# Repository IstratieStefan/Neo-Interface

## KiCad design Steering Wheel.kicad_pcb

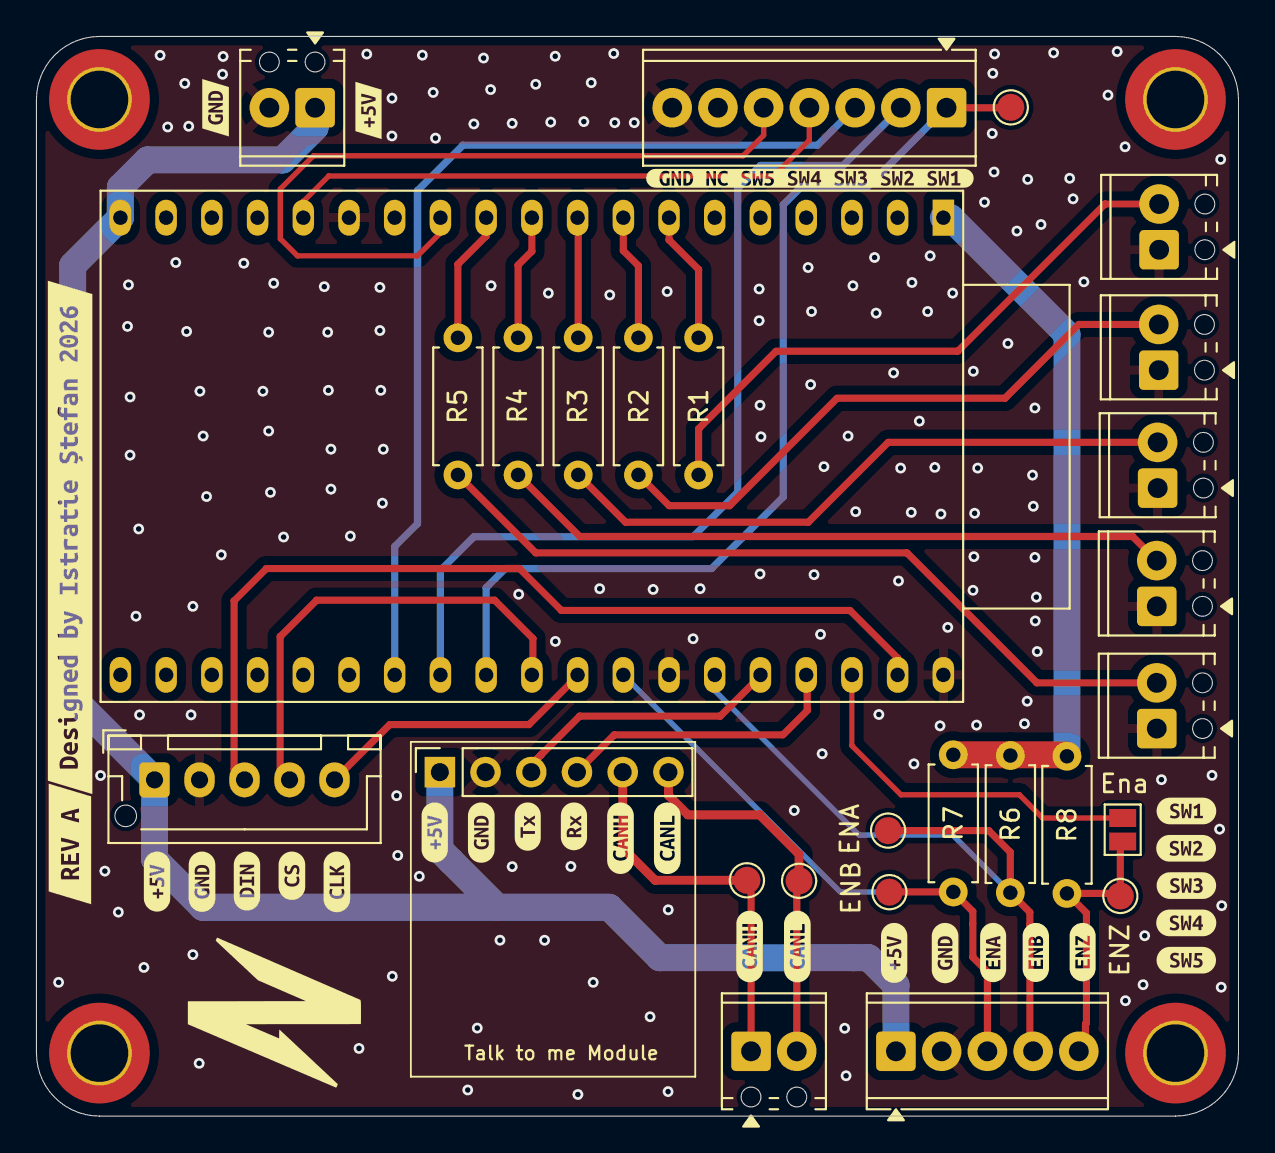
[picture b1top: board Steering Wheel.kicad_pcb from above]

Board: 2 copper layers, 66.8 x 60.0 mm, 60 parts (1 on the bottom side), 29 nets.

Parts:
H1, H2, H3, H4: MountingHole; MountingHole_3.2mm_M3_DIN965_Pad_TopBottom
J1: Conn_01x06_Socket; PinSocket_1x06_P2.54mm_Vertical
J2, J4: Screw_Terminal_01x02; TerminalBlock_Phoenix_MPT-0,5-2-2.54_1x02_P2.54mm_Horizontal
J3: Screw_Terminal_01x05; TerminalBlock_Phoenix_MPT-0,5-5-2.54_1x05_P2.54mm_Horizontal
J5: Conn_01x05_Socket; JST_XH_B5B-XH-AM_1x05_P2.50mm_Vertical
JP1: SolderJumper_2_Open; SolderJumper-2_P1.3mm_Open_Pad1.0x1.5mm
R1, R2, R3, R4, R5: 220; R_Axial_DIN0207_L6.3mm_D2.5mm_P7.62mm_Horizontal
R6, R7, R8: 4.7k; R_Axial_DIN0207_L6.3mm_D2.5mm_P7.62mm_Horizontal
SW1, SW2, SW3, SW4, SW5: SW_Push; TerminalBlock_Phoenix_MPT-0,5-2-2.54_1x02_P2.54mm_Horizontal
SW6: SW_Rotary_1x6_MP; TerminalBlock_Phoenix_MPT-0,5-7-2.54_1x07_P2.54mm_Horizontal
SW7: SW_Rotary_1x5_MP; TestPoint_Pad_D1.5mm
TP1, TP2, TP3, TP4, TP5: TestPoint; TestPoint_Pad_D1.5mm
U2: ESP32-DevKitC; ESP32 DevKitC
kibuzzard-696A0FA7: G***; kibuzzard-696A0FA7
kibuzzard-696A0FB0: G***; kibuzzard-696A0FB0
kibuzzard-69662E8F: G***; kibuzzard-69662E8F
kibuzzard-69662E9B: G***; kibuzzard-69662E9B
kibuzzard-69662E70: G***; kibuzzard-69662E70
kibuzzard-69662E83: G***; kibuzzard-69662E83
kibuzzard-69662EA7, kibuzzard-69662EA7#2, kibuzzard-69662EA7#3: G***; kibuzzard-69662EA7
kibuzzard-697744E1: G***; kibuzzard-697744E1
kibuzzard-697744F1: G***; kibuzzard-697744F1
kibuzzard-697744FD: G***; kibuzzard-697744FD
kibuzzard-697747A7: G***; kibuzzard-697747A7
kibuzzard-697747AD: G***; kibuzzard-697747AD
kibuzzard-697747B3: G***; kibuzzard-697747B3
kibuzzard-697747CE: G***; kibuzzard-697747CE
kibuzzard-697747DE: G***; kibuzzard-697747DE
kibuzzard-697749A6: G***; kibuzzard-697749A6
kibuzzard-6966322B: G***; kibuzzard-6966322B
kibuzzard-6966323F: G***; kibuzzard-6966323F
kibuzzard-6966324D: G***; kibuzzard-6966324D
kibuzzard-6977479D: G***; kibuzzard-6977479D
kibuzzard-6977488C: G***; kibuzzard-6977488C
kibuzzard-6977589B: G***; kibuzzard-6977589B
kibuzzard-69663236: G***; kibuzzard-69663236
kibuzzard-69663259: G***; kibuzzard-69663259
kibuzzard-69774506: G***; kibuzzard-69774506
kibuzzard-69774561: G***; kibuzzard-69774561
kibuzzard-69775305: G***; kibuzzard-69775305

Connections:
+3.3V: R6.1, R7.1, R8.1, U2.1 (3V3)
+5V: J1.1, J3.1, J4.1, J5.1, U2.19 (5V)
/Button1: R1.2, U2.7 (32K_XP/GPIO32/ADC1_CH4)
/Button2: R2.2, U2.8 (32K_XN/GPIO33/ADC1_CH5)
/Button3: R3.2, U2.9 (DAC_1/ADC2_CH8/GPIO25)
/Button4: R4.2, U2.10 (DAC_2/ADC2_CH9/GPIO26)
/Button5: R5.2, U2.11 (ADC2_CH7/GPIO27)
/CANH: J1.5, J2.1, TP4.1
/CANL: J1.6, J2.2, TP5.1
/CLK: J5.5, U2.30 (GPIO18)
/CS: J5.4, U2.29 (GPIO5)
/DIN: J5.3, U2.37 (GPIO23)
/EncoderA: J3.3, R7.2, TP1.1, U2.31 (GPIO19)
/EncoderB: J3.4, R6.2, TP2.1, U2.33 (GPIO21)
/EncoderZ: J3.5, JP1.2 (B), R8.2, TP3.1
/Rx: J1.3, U2.34 (U0RXD/GPIO3)
/SW1: SW6.1, SW7.1, U2.28 (GPIO17)
/SW2: SW6.2, U2.27 (GPIO16)
/SW3: SW6.3, U2.26 (ADC2_CH0/GPIO4)
/SW4: SW6.4, U2.15 (MTCK/GPIO13/ADC2_CH4)
/SW5: SW6.5, U2.12 (MTMS/GPIO14/ADC2_CH6)
/Tx: J1.4, U2.35 (U0TXD/GPIO1)
GND: J1.2, J3.2, J4.2, J5.2, SW1.1, SW2.1, SW3.1, SW4.1, SW5.1, SW6.7, U2.14 (GND), U2.32 (GND), U2.38 (GND)
unnamed: JP1.1 (A), U2.36 (GPIO22)
unnamed: R1.1, SW1.2
unnamed: R2.1, SW2.2
unnamed: R3.1, SW3.2
unnamed: R4.1, SW4.2
unnamed: R5.1, SW5.2

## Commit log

2026-01-27 repo uplaod
2026-01-28 Via stitching
2026-02-02 Gerbers
2026-02-04 made in update
2026-02-04 Gerber compressed
